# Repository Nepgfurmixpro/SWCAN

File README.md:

# SWCAN Reader
This project defines a schematic and pcb of a small single board SWCAN reader using USB CDC for computer communication and a TH8056 as the transciever, utilizing a STM32 MCU as the boards brain. The board includes a SWD header to allow for initial programming, future programming possible through DFU using the bootloader.

This board is in development and may see changes.

### Software Used
* KiCAD 10
* STM32CubeMX
* STM32CubeProgrammer
* CLion
* CMake

The STM32 MCU is a STM32G491KCU6

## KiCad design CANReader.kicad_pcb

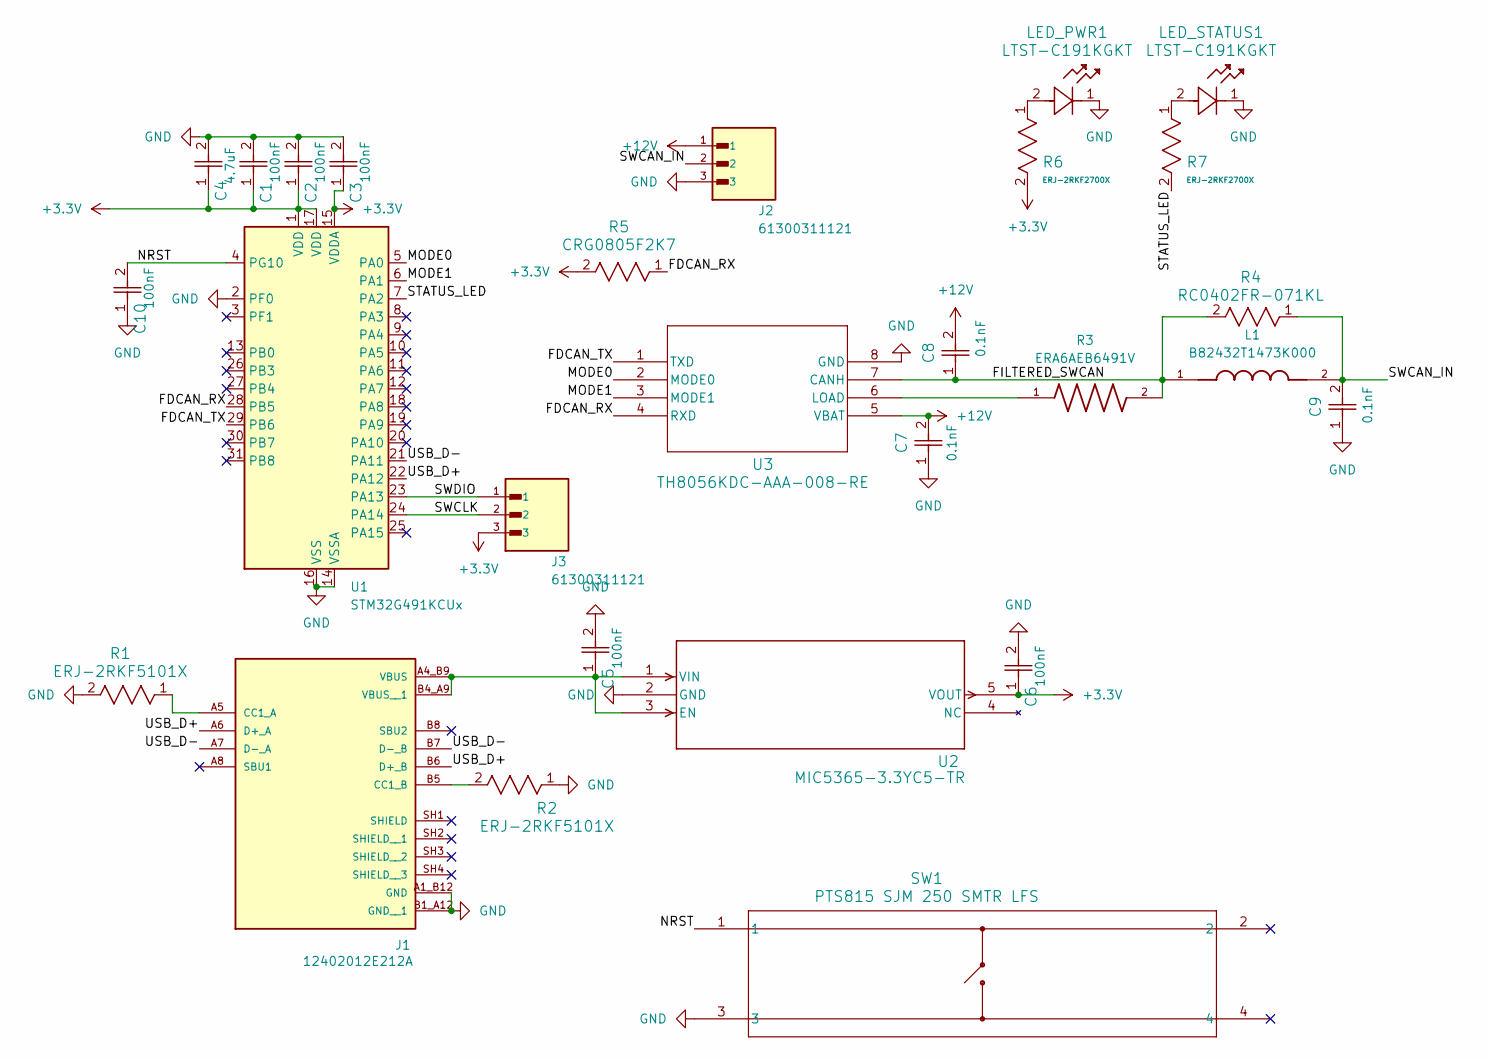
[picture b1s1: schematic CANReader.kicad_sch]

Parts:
C1, C2, C3, C5, C6, C10: CL05B104KP5NNNC; CAP_CL05_SAM-L
C4: CL05A475MP5NRNC; CAP_CL05_SAM
C7, C8, C9: CL05C101JB5NNNC; CAP_CL05_SAM
J1: 12402012E212A; AMPHENOL_12402012E212A; PARTREV 4
J2, J3: 61300311121; WURTH_61300311121; PARTREV 003.001
L1: B82432T1473K000; INDM4532X340N; PARTREV N/A
LED_PWR1: LTST-C191KGKT; LED_LTST-C191KGKT_LTO-L
LED_STATUS1: LTST-C191KGKT; LED_LTST-C191KGKT_LTO-L
R1, R2: ERJ-2RKF5101X; RC0402N_PAN-L
R3: ERA6AEB6491V; RES_ERA6AEB6491V; PARTREV 3/1/2020
R4: RC0402FR-071KL; RC0402N_YAG-L
R5: CRG0805F2K7; RES0805_CRG_TYCO_TYC-L
R6, R7: ERJ-2RKF2700X; RC0402N_PAN
SW1: PTS815 SJM 250 SMTR LFS; SW4_PTS815_SJM_250_SMTR_LFS_CNK
U1: STM32G491KCUx; QFN-32-1EP_5x5mm_P0.5mm_EP3.45x3.45mm_ThermalVias
U2: MIC5365-3.3YC5-TR; SC-70_C5_MCH-L
U3: TH8056KDC-AAA-008-RE; MEL_SOIC-8_MEL-L

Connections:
+3.3V: C1.1, C2.1, C3.1, C4.1, C6.1, J3.3, R5.2, R6.2, U1.1 (VDD), U1.15 (VDDA), U1.17 (VDD), U2.5 (VOUT)
+12V: C7.2, C8.2, J2.1, U3.5 (VBAT)
/FDCAN_RX: R5.1, U1.28 (PB5), U3.4 (RXD)
/FDCAN_TX: U1.29 (PB6), U3.1 (TXD)
/FILTERED_SWCAN: C8.1, L1.1, R3.2, R4.2, U3.7 (CANH)
/MODE0: U1.5 (PA0), U3.2 (MODE0)
/MODE1: U1.6 (PA1), U3.3 (MODE1)
/NRST: C10.2, SW1.1, U1.4 (PG10)
/STATUS_LED: R7.2, U1.7 (PA2)
/SWCAN_IN: C9.2, J2.2, L1.2, R4.1
/SWCLK: J3.2, U1.24 (PA14)
/SWDIO: J3.1, U1.23 (PA13)
/USB_D+: J1.A6 (D+_A), J1.B6 (D+_B), U1.22 (PA12)
/USB_D-: J1.A7 (D-_A), J1.B7 (D-_B), U1.21 (PA11)
GND: C1.2, C2.2, C3.2, C4.2, C5.2, C6.2, C7.1, C9.1, C10.1, J1.A1_B12 (GND), J1.B1_A12 (GND__1), J2.3, LED_PWR1.1, LED_STATUS1.1, R1.2, R2.1, SW1.3, U1.2 (PF0), U1.14 (VSSA), U1.16 (VSS), U1.32 (VSS), U1.33 (VSS), U2.2 (GND), U3.8 (GND)
unnamed: J1.A5 (CC1_A), R1.1
unnamed: J1.B5 (CC1_B), R2.2
unnamed: C5.1, J1.A4_B9 (VBUS), J1.B4_A9 (VBUS__1), U2.1 (VIN), U2.3 (EN)
unnamed: LED_PWR1.2, R6.1
unnamed: LED_STATUS1.2, R7.1
unnamed: R3.1, U3.6 (LOAD)

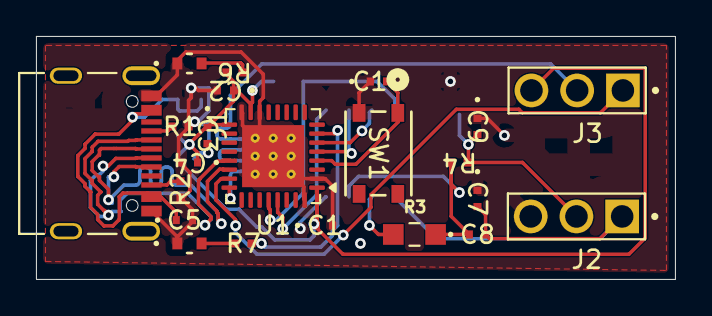
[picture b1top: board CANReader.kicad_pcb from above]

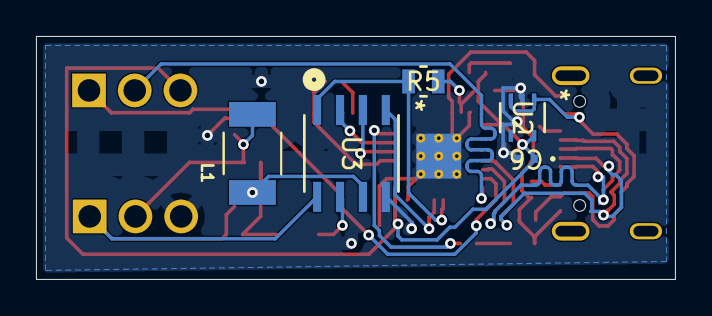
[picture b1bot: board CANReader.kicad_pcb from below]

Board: 2 copper layers, 35.5 x 13.5 mm, 27 parts (5 on the bottom side), 21 nets.

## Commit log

2026-05-30 Remove lck files
2026-05-30 Remove built .zip gerber files
2026-05-30 Add bom to gitignore
